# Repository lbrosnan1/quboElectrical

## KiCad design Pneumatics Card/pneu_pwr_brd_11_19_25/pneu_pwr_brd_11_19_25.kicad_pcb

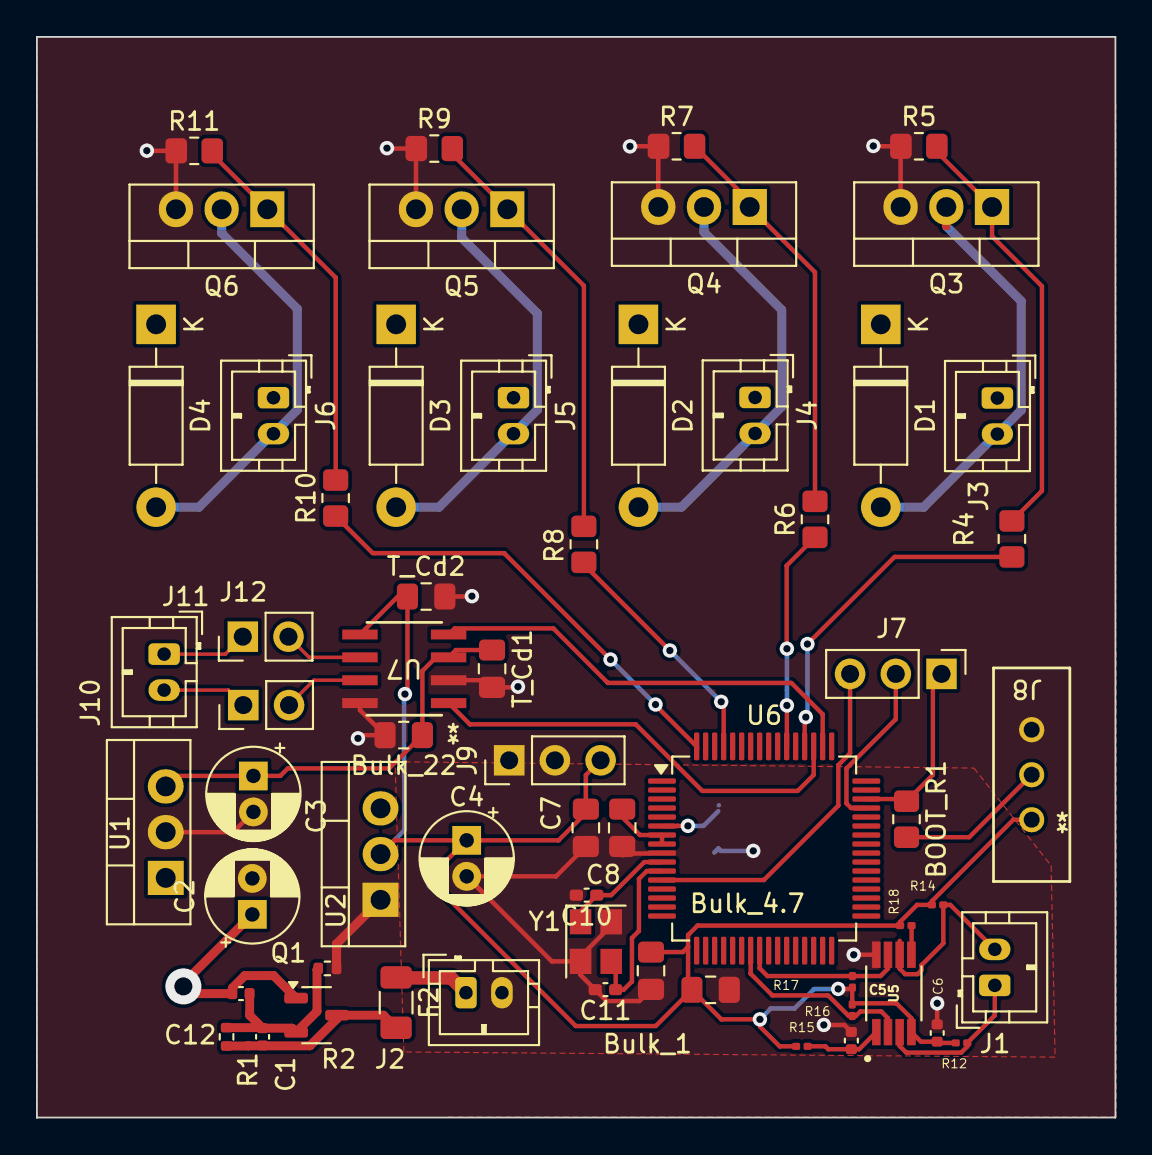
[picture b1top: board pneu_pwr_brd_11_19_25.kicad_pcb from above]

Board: 4 copper layers, 59.9 x 60.0 mm, 62 parts (1 on the bottom side), 36 nets.

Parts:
BOOT_R1: 10k; R_0805_2012Metric_Pad1.20x1.40mm_HandSolder
Bulk_1: 1uF; C_0805_2012Metric_Pad1.18x1.45mm_HandSolder
Bulk_4.7: 4.7uF; C_0805_2012Metric_Pad1.18x1.45mm_HandSolder
Bulk_22: 22uF; C_0805_2012Metric_Pad1.18x1.45mm_HandSolder
C1, C12: 4.7u; C_0402_1005Metric
C2, C3, C4: 10u; CP_Radial_D5.0mm_P2.00mm
C5, C6: 0.1u; C_0402_1005Metric
C7, C8, C9: 100nF; C_0805_2012Metric_Pad1.18x1.45mm_HandSolder
C10, C11: 10pF; C_0402_1005Metric_Pad0.74x0.62mm_HandSolder
D1, D2, D3, D4: 1N47xxA; D_DO-41_SOD81_P10.16mm_Horizontal
F2: 10A; Fuse_1206_3216Metric
J1, J2, J3, J4, J5, J6, J12: 2X1; JST_PH_B2B-PH-K_1x02_P2.00mm_Vertical
J7, J9: Conn_01x03_Pin; PinHeader_1x03_P2.54mm_Vertical
J8: Conn_01x03; slide_switch_EGER1218_Thruster
J10, J11: Conn_01x02; PinHeader_1x02_P2.54mm_Vertical
Q1: NTR0202PLT1G; SOT-23-3
Q3, Q4, Q5, Q6: FQP30N06L; TO-220-3_Vertical
R1: 47k; R_0402_1005Metric
R2: 100; R_0402_1005Metric
R4, R6, R8, R10: 330; R_0805_2012Metric_Pad1.20x1.40mm_HandSolder
R5, R7, R9, R11: 10k; R_0805_2012Metric_Pad1.20x1.40mm_HandSolder
R12, R14, R15, R16, R17, R18: 10k; C_0201_0603Metric
T_Cd1, T_Cd2: 100nF; C_0805_2012Metric_Pad1.18x1.45mm_HandSolder
U1: L7805; TO-220-3_Vertical
U2: LD1117V33; TO-220-3_Vertical
U5: TCA4307; SOP65P490X110-8N
U6: STM32G0B1RETx; LQFP-64_10x10mm_P0.5mm
U7: ATA6561-GAQW-N; SOIC8_4P9X3P9MC_MCH
Y1: 16Mhz; Crystal_SMD_3225-4Pin_3.2x2.5mm

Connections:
3.3V: Bulk_1.2, Bulk_4.7.1, C4.1, C6.2, C7.1, C8.1, J8.1, J9.3, R12.2, R14.1, R15.1, R16.2, R17.1, R18.1, T_Cd2.1, U2.2 (VO), U5.4 (VCC), U6.7 (VREF+), U6.8 (VDD), U7.5 (VIO)
5V: Bulk_22.1, C3.1, T_Cd1.1, U1.3 (OUT), U7.3 (VCC)
12V: C2.1, C12.2, D1.1 (K), D2.1 (K), D3.1 (K), D4.1 (K), J3.1, J4.1, J5.1, J6.1, Q1.1 (D), U1.1 (IN), U2.3 (VI)
+12V_fuse: F2.1, J2.1
/NRST: J7.3, U6.12 (PF2)
/SWCLK: BOOT_R1.1, J7.1, U6.46 (PA14)
/SWDIO: J7.2, U6.45 (PA13)
CAN+: J10.1, J10.2, J12.2, U7.7 (CANH)
CAN-: J11.1, J11.2, J12.1, U7.6 (CANL)
FDCAN_RX: U6.50 (PD0), U7.4 (RXD)
FDCAN_TX: U6.51 (PD1), U7.1 (TXD)
GND: Bulk_1.1, Bulk_4.7.2, Bulk_22.2, C2.2, C3.2, C4.2, C5.1, C6.1, C7.2, C8.2, C9.1, C10.2, C11.2, J2.2, J8.3, J9.1, J9.2, Q3.3 (S), Q4.3 (S), Q5.3 (S), Q6.3 (S), R2.1, R5.1, R7.1, R9.1, R11.1, T_Cd1.2, T_Cd2.2, U1.2 (GND), U2.1 (GND), U5.8 (GND), U6.9 (VSS), U7.2 (GND), U7.8 (STBY), Y1.2, Y1.4
unnamed: BOOT_R1.2, J8.2
unnamed: C1.1, C12.1, Q1.2 (G), R1.1, R2.2
unnamed: C1.2, F2.2, Q1.3 (S), R1.2
unnamed: Q3.1 (G), R4.2, R5.2
unnamed: Q4.1 (G), R6.2, R7.2
unnamed: Q5.1 (G), R8.2, R9.2
unnamed: Q6.1 (G), R10.2, R11.2
unnamed: C5.2, R15.2, U5.1 (EN)
unnamed: R18.2, U5.5 (READY)
RCC_OSC_IN: C10.1, U6.10 (PF0), Y1.1
RCC_OSC_OUT: C11.1, U6.11 (PF1), Y1.3
S1CTRL: R4.1, U6.52 (PD2)
S2CTRL: R6.1, U6.54 (PD4)
S3CTRL: R8.1, U6.61 (PB7)
S4CTRL: R10.1, U6.64 (PC10)
SCL: R17.2, U5.7 (SCLOUT), U6.24 (PA7)
SCL_ext: J1.2, R14.2, U5.6 (SCLIN)
SDA: R16.1, U5.2 (SDAOUT), U6.23 (PA6)
SDA_ext: J1.1, R12.1, U5.3 (SDAIN)
SLN1-: D1.2 (A), J3.2, Q3.2 (D)
SLN2-: D2.2 (A), J4.2, Q4.2 (D)
SLN3-: D3.2 (A), J5.2, Q5.2 (D)
SLN4-: D4.2 (A), J6.2, Q6.2 (D)
VBAT: C9.2, U6.6 (VBAT)

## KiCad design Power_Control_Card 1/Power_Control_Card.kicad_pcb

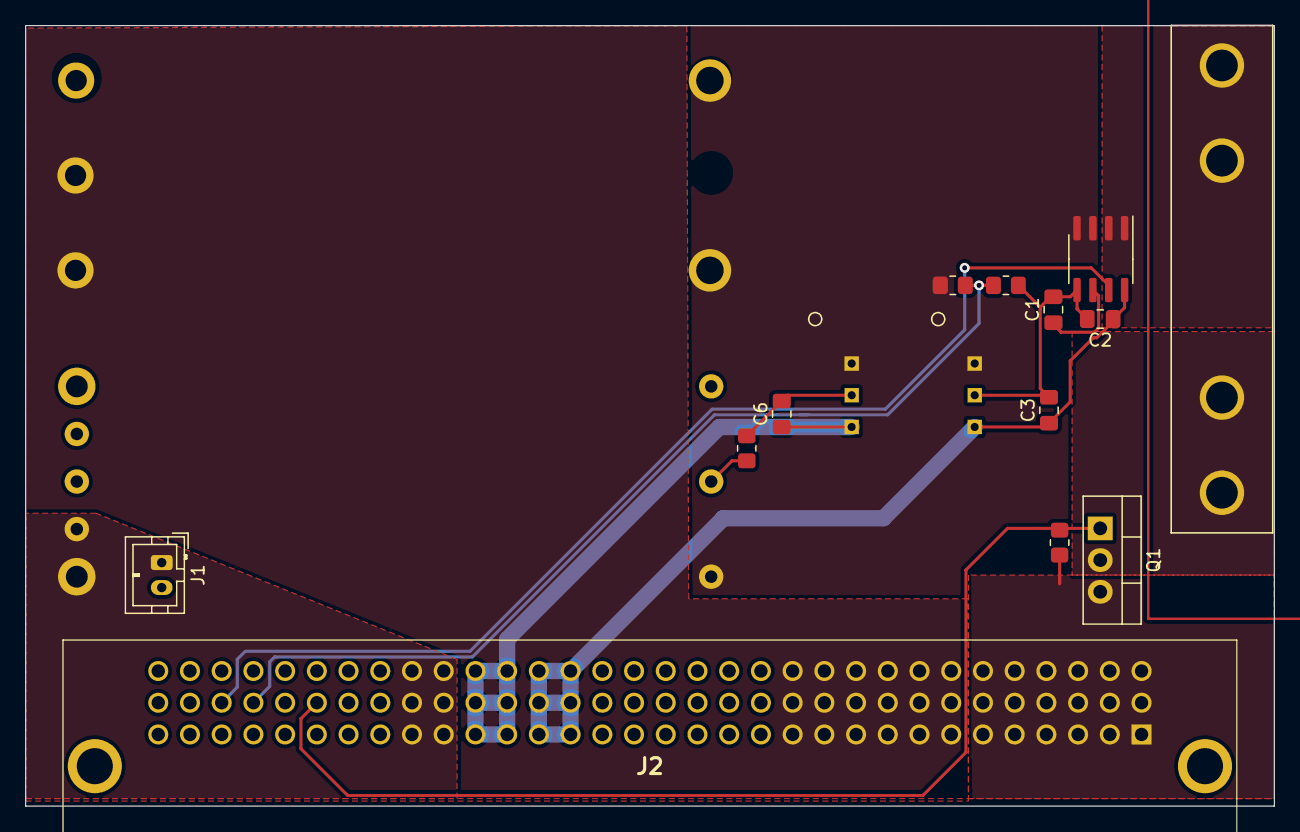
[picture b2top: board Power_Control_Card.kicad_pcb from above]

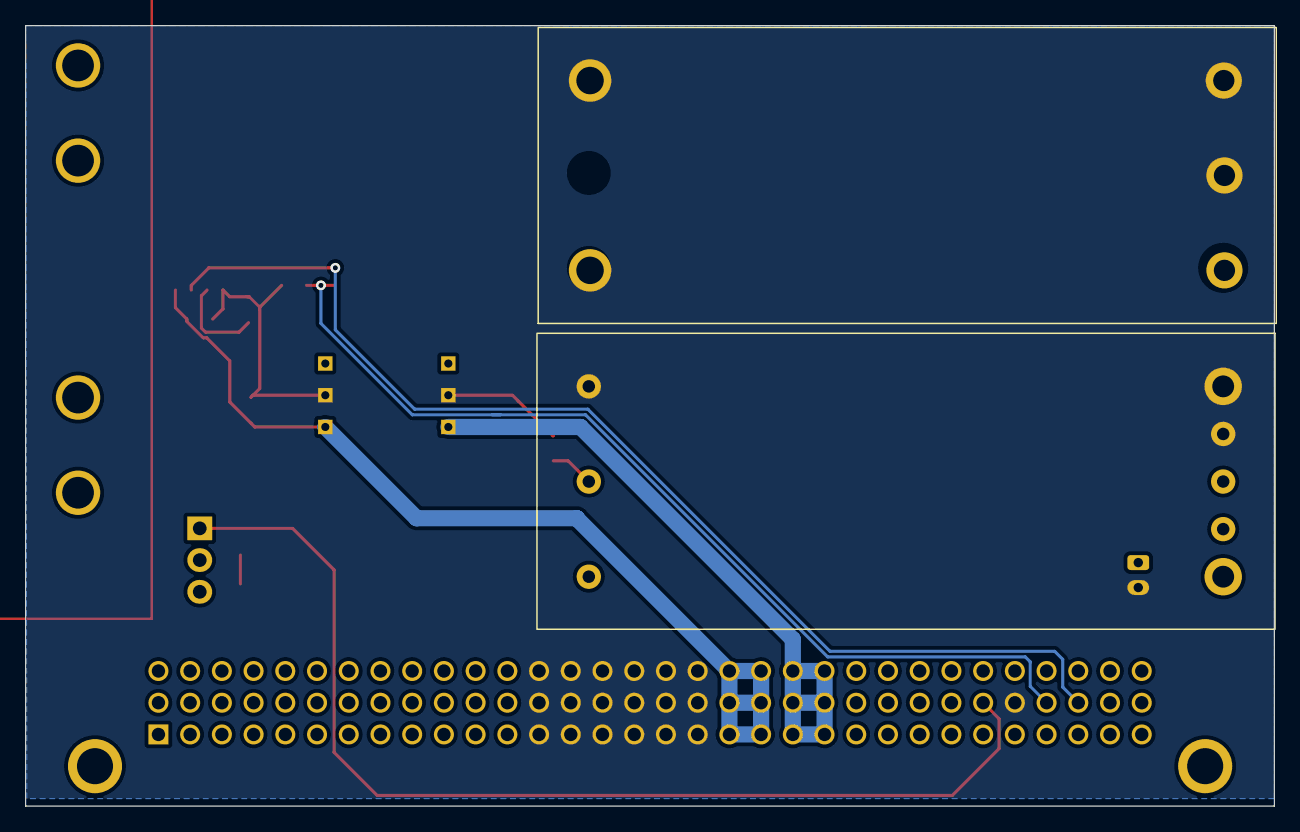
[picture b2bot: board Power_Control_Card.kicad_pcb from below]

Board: 2 copper layers, 100.0 x 62.5 mm, 17 parts (2 on the bottom side), 14 nets.

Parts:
20A1: Fuse; 1.25__FUSECLIPS
C1: 47n; C_0805_2012Metric_Pad1.18x1.45mm_HandSolder
C2: 0.1u; C_0805_2012Metric_Pad1.18x1.45mm_HandSolder
C3, C6: 1u; C_0805_2012Metric_Pad1.18x1.45mm_HandSolder
DC/DC_CNVRT1: TSR2-2450; TSR2
DC/DC_CNVRT2: TSR2-2433; TSR2
INPT_CRRNT_SNSR1: TMCS1101A4B; SOIC-8_3.9x4.9mm_P1.27mm
J1: Conn_01x02; JST_PH_B2B-PH-K_1x02_P2.00mm_Vertical
J2: 6509475
Q1: FQPF27P06; TO-220-3_Vertical
RSW1, RSW2: 10kO; R_0805_2012Metric_Pad1.20x1.40mm_HandSolder
U1: 240W_CONV
U2: 72W_CONV
VDIV1(R)1: 90kO; R_0805_2012Metric_Pad1.20x1.40mm_HandSolder
VDIV2(R)1: 10kO; R_0805_2012Metric_Pad1.20x1.40mm_HandSolder

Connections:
12V_Jetson: J1.1, J2.A23, J2.A24, J2.B23, J2.B24, J2.C23, J2.C24, U2.7 (SENSE+), U2.8 (VOUT)
+3.3V: C6.1, DC/DC_CNVRT2.3 (+V_OUT), J2.A21, J2.A22, J2.B21, J2.B22, J2.C21, J2.C22
+5V: C2.1, C3.1, DC/DC_CNVRT1.3 (+V_OUT), INPT_CRRNT_SNSR1.8 (VCC), J2.A19, J2.A20, J2.B19, J2.B20, J2.C19, J2.C20
+12V: J2.A7, J2.A8, J2.A9, J2.A10, J2.A11, J2.A12, J2.B7, J2.B8, J2.B9, J2.B10, J2.B11, J2.B12, J2.C7, J2.C8, J2.C9, J2.C10, J2.C11, J2.C12, U1.8 (VOUT)
+24V: J2.A1, J2.A2, J2.A3, J2.A4, J2.A5, J2.A6, J2.B1, J2.B2, J2.B3, J2.B4, J2.B5, J2.B6, J2.C1, J2.C2, J2.C3, J2.C4, J2.C5, J2.C6, Q1.3 (S), RSW1.1
/VBATT: 20A1.P$2 (4), INPT_CRRNT_SNSR1.1 (IP+)
/V_POWER: DC/DC_CNVRT1.1 (+V_IN), DC/DC_CNVRT2.1 (+V_IN), INPT_CRRNT_SNSR1.3 (IP-), U1.1 (VIN), U2.1 (VIN), VDIV1(R)1.1
DAT1: J2.B29, VDIV1(R)1.2, VDIV2(R)1.1
DAT2: INPT_CRRNT_SNSR1.7 (VIOUT), J2.B30
unnamed: 20A1.P$1 (1), Q1.2 (D)
unnamed: C1.1, INPT_CRRNT_SNSR1.6 (FILTER)
unnamed: RSW2.1, U2.2 (ON/OFF)
SW1: C1.2, C2.2, C3.2, C6.2, DC/DC_CNVRT1.2 (GND), DC/DC_CNVRT2.2 (GND), INPT_CRRNT_SNSR1.5 (GND), J1.2, J2.A13, J2.A14, J2.A15, J2.A16, J2.A17, J2.A18, J2.B13, J2.B14, J2.B15, J2.B16, J2.B17, J2.B18, J2.B28, J2.C13, J2.C14, J2.C15, J2.C16, J2.C17, J2.C18, RSW2.2, U1.3 (IN-), U1.4 (OUT-), U2.3 (IN-), U2.4 (OUT-), U2.5 (SENSE-), VDIV2(R)1.2
SW2: J2.B27, Q1.1 (G), RSW1.2

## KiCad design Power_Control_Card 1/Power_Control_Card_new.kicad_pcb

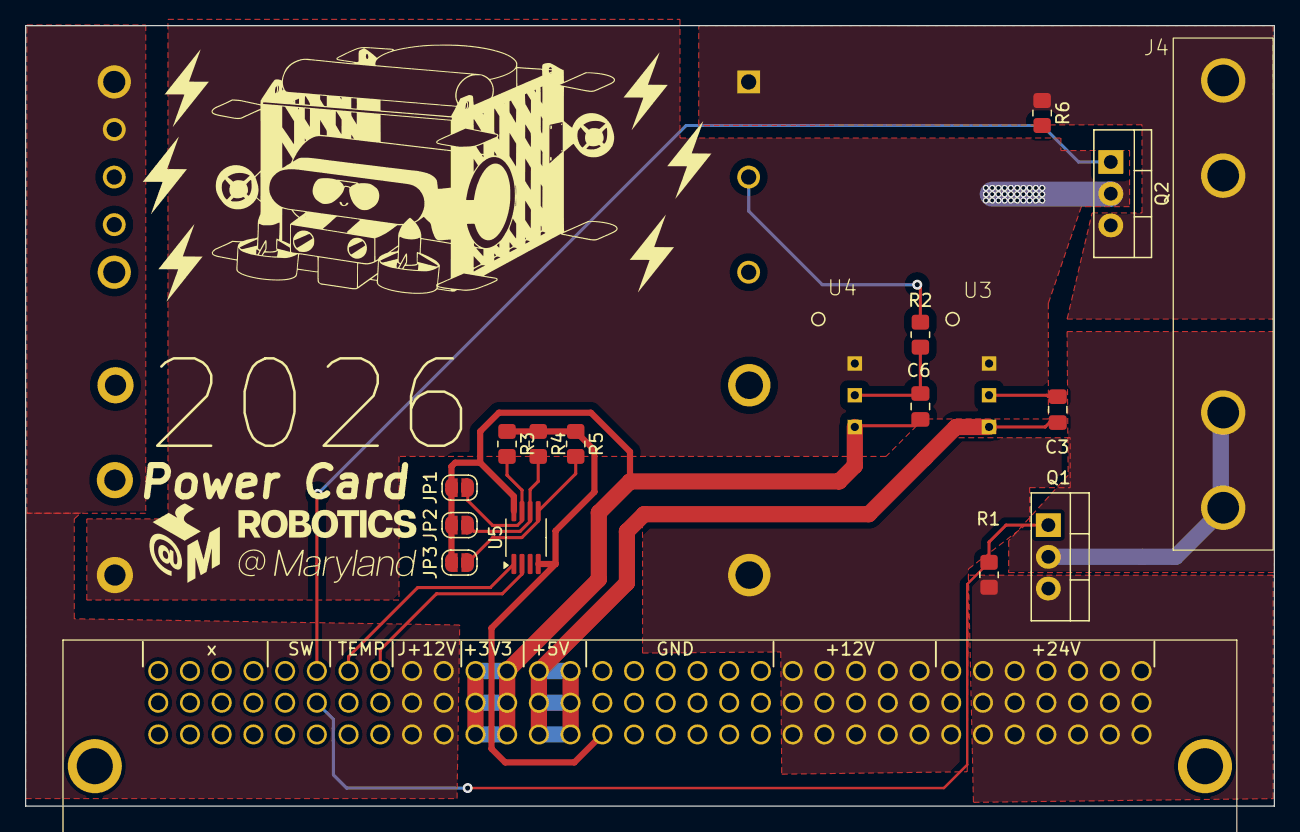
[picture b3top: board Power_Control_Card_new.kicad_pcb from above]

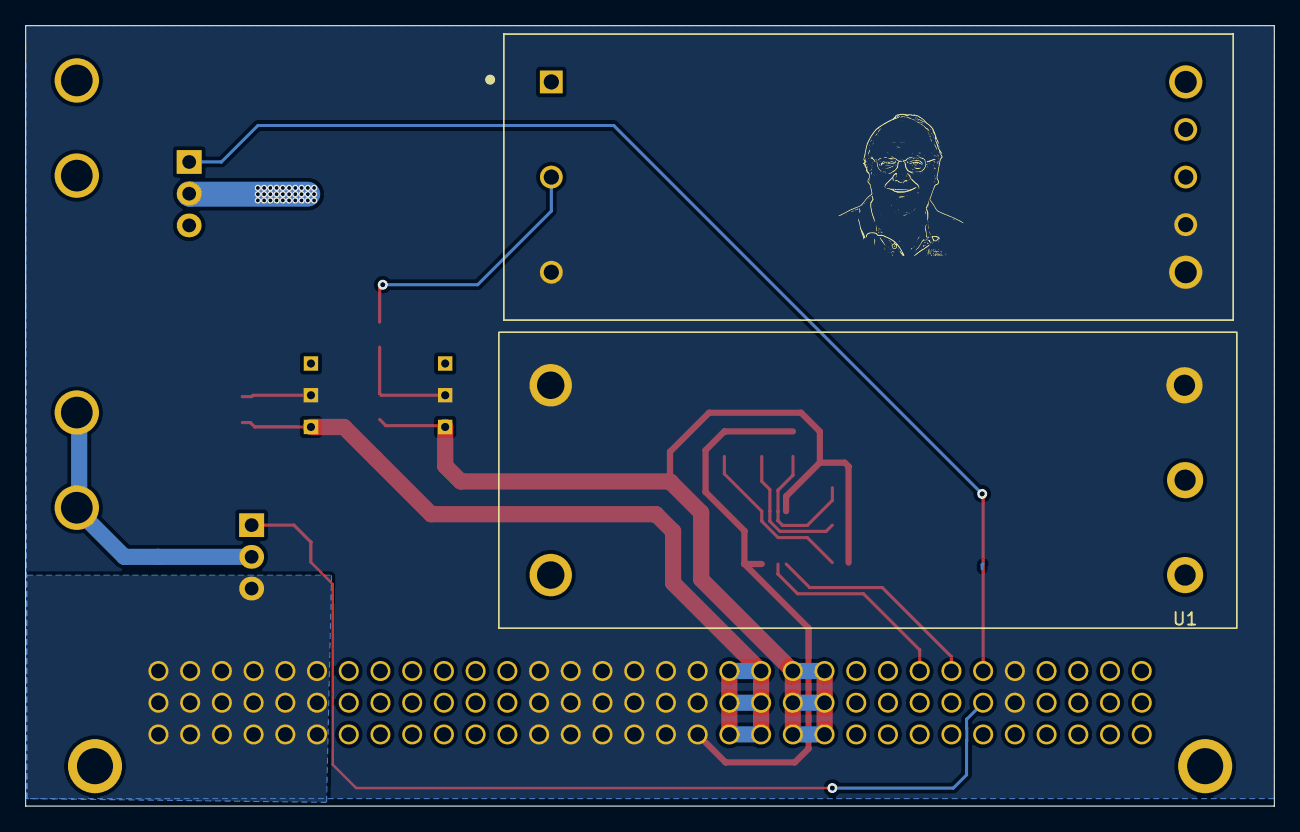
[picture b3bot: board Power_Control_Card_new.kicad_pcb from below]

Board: 2 copper layers, 100.0 x 62.5 mm, 20 parts (2 on the bottom side), 17 nets.

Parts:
C3, C6: 1u; C_0805_2012Metric_Pad1.18x1.45mm_HandSolder
J2: 6509475
J4: Conn_01x04_Pin; 1.25__FUSECLIPS
JP1, JP2, JP3: SolderJumper_2_Open; SolderJumper-2_P1.3mm_Open_RoundedPad1.0x1.5mm
Q1, Q2: FQPF27P06; TO-220-3_Vertical
R1, R2, R6: 10kO; R_0805_2012Metric_Pad1.20x1.40mm_HandSolder
R3, R4, R5: temp R; R_0805_2012Metric_Pad1.20x1.40mm_HandSolder
U1: 240W_CONV
U2: CONV_UWE-24_3-Q12P-C
U3: TSR2-2450; TSR2
U4: TSR2-2433; TSR2
U5: MCP9808_MSOP; MSOP-8_3x3mm_P0.65mm

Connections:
12V_Jetson: J2.A23, J2.A24, J2.B23, J2.B24, J2.C23, J2.C24, U2.7 (SENSE+), U2.8 (VOUT)
+3.3V: C6.1, J2.A21, J2.A22, J2.B21, J2.B22, J2.C21, J2.C22, JP1.1 (A), JP2.1 (A), JP3.1 (A), U4.3 (+V_OUT), U5.8 (V_{DD})
+5V: C3.1, J2.A19, J2.A20, J2.B19, J2.B20, J2.C19, J2.C20, U3.3 (+V_OUT)
+12V: J2.A7, J2.A8, J2.A9, J2.A10, J2.A11, J2.A12, J2.B7, J2.B8, J2.B9, J2.B10, J2.B11, J2.B12, J2.C7, J2.C8, J2.C9, J2.C10, J2.C11, J2.C12, U1.8 (VOUT)
+24V: J2.A1, J2.A2, J2.A3, J2.A4, J2.A5, J2.A6, J2.B1, J2.B2, J2.B3, J2.B4, J2.B5, J2.B6, J2.C1, J2.C2, J2.C3, J2.C4, J2.C5, J2.C6, Q1.3 (S), R1.1
/NonJetsonPower: Q2.2 (D), U1.1 (VIN), U3.1 (+V_IN), U4.1 (+V_IN)
/VBATT: J4.3, J4.4, Q2.3 (S), R6.1, U2.1 (VIN)
GND: C3.2, C6.2, J2.A13, J2.A14, J2.A15, J2.A16, J2.A17, J2.A18, J2.B13, J2.B14, J2.B15, J2.B16, J2.B17, J2.B18, J2.B28, J2.C13, J2.C14, J2.C15, J2.C16, J2.C17, J2.C18, J2.C28, R2.2, R3.1, R4.1, R5.1, U1.3 (IN-), U1.4 (OUT-), U2.3 (IN-), U2.4 (OUT-), U2.5 (SENSE-), U3.2 (GND), U4.2 (GND), U5.4 (GND)
NJSW1: J2.C27, Q2.1 (G), R6.2
unnamed: J4.1, J4.2, Q1.2 (D)
unnamed: JP1.2 (B), R3.2, U5.7 (A0)
unnamed: JP2.2 (B), R4.2, U5.6 (A1)
unnamed: JP3.2 (B), R5.2, U5.5 (A2)
unnamed: R2.1, U2.2 (ON/OFF)
SCL2: J2.C25, U5.2 (SCL)
SDA2: J2.C26, U5.1 (SDA)
SW2: J2.B27, Q1.1 (G), R1.2

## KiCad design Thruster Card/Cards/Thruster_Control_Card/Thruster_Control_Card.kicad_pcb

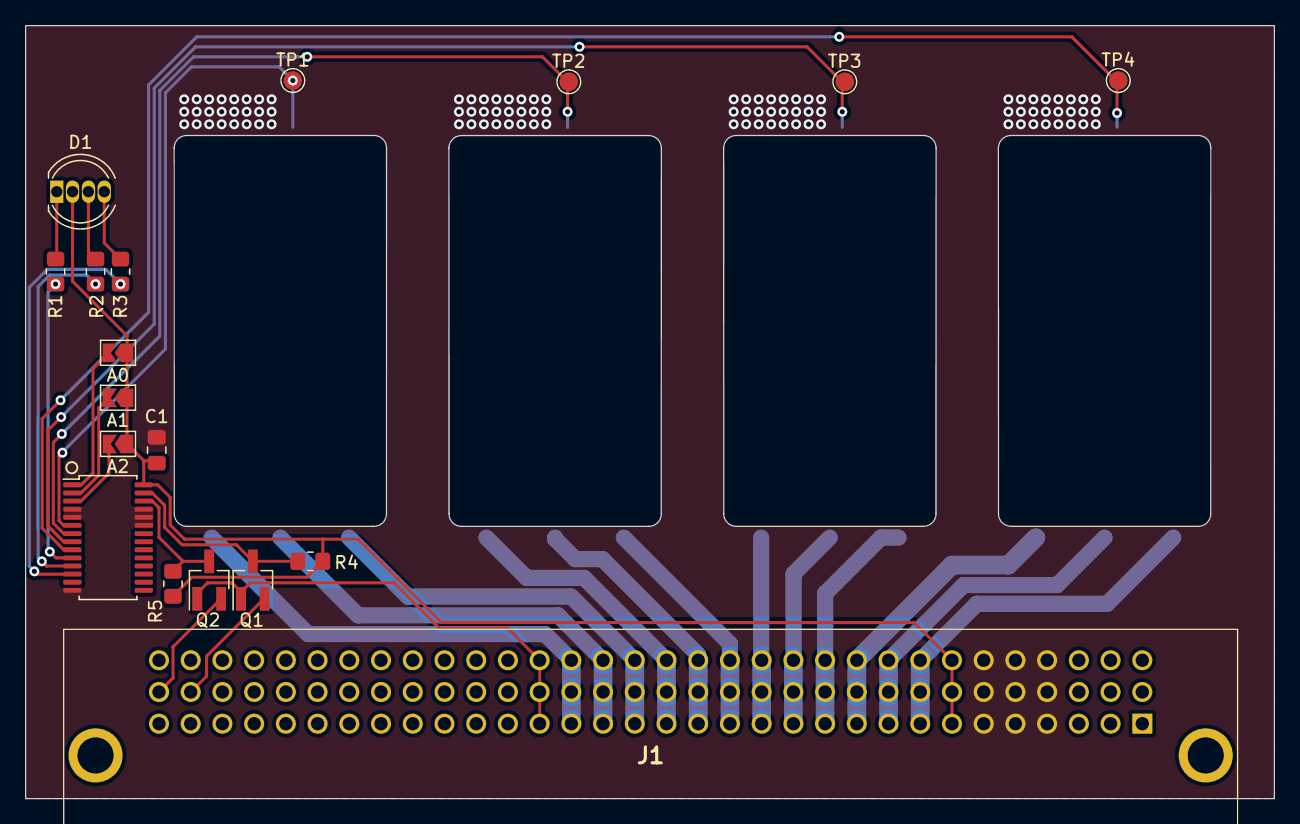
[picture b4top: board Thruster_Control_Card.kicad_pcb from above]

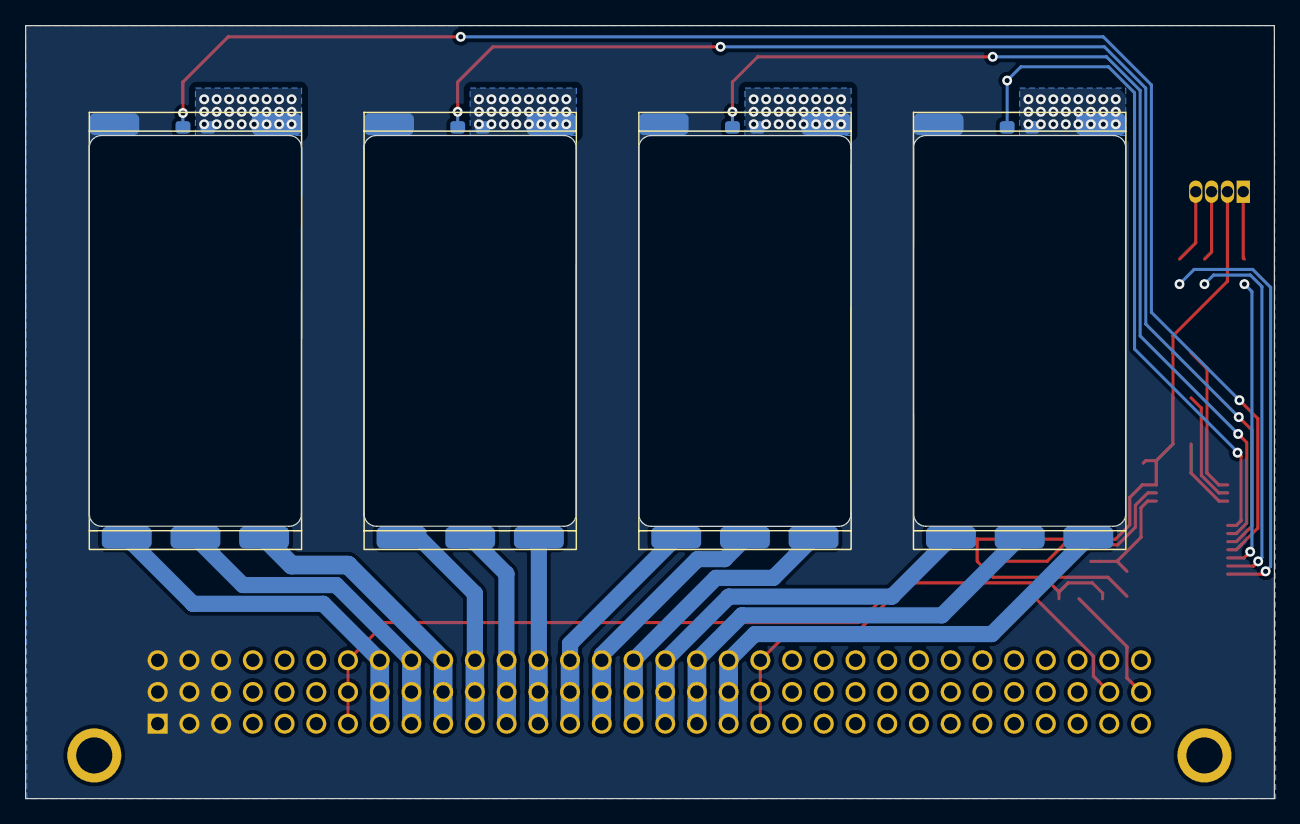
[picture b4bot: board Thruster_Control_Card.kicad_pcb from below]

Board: 4 copper layers, 100.0 x 61.9 mm, 22 parts (4 on the bottom side), 33 nets.

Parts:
A0, A1, A2: SolderJumper_2_Open; SolderJumper-2_P1.3mm_Open_TrianglePad1.0x1.5mm
C1: 10u; C_0805_2012Metric_Pad1.18x1.45mm_HandSolder
D1: LED_RGAB; LED_D5.0mm-4_RGB
I2C_PWM_DRIVER1: PCA9685; TSSOP-28_4.4x9.7mm_P0.65mm
J1: 6509475
Q1, Q2: BSS138; SOT-23_Handsoldering
R1, R2, R3: 220; R_0805_2012Metric_Pad1.20x1.40mm_HandSolder
R4, R5: 4.7kO; R_0805_2012Metric_Pad1.20x1.40mm_HandSolder
TP1, TP2, TP3, TP4: TestPoint; TestPoint_Pad_D1.5mm
U1, U2, U3, U4: ESC

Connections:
+3.3V: J1.A20, J1.B20, J1.C20, Q1.1 (G), Q2.1 (G)
+5V: A0.1 (A), A1.1 (A), A2.1 (A), C1.1, D1.2 (A), I2C_PWM_DRIVER1.28 (VDD), J1.A7, J1.B7, J1.C7, R4.2, R5.1
+12V: J1.A1, J1.A2, J1.A3, J1.B1, J1.B2, J1.B3, J1.C1, J1.C2, J1.C3, U1.1 (Vcc), U2.1 (Vcc), U3.1 (Vcc), U4.1 (Vcc)
/A1: J1.A17, J1.B17, J1.C17, U1.3 (A)
/A2: J1.A14, J1.B14, J1.C14, U2.3 (A)
/A3: J1.A11, J1.B11, J1.C11, U3.3 (A)
/A4: J1.A8, J1.B8, J1.C8, U4.3 (A)
/B1: J1.A18, J1.B18, J1.C18, U1.4 (B)
/B2: J1.A15, J1.B15, J1.C15, U2.4 (B)
/B3: J1.A12, J1.B12, J1.C12, U3.4 (B)
/B4: J1.A9, J1.B9, J1.C9, U4.4 (B)
/C1: J1.A19, J1.B19, J1.C19, U1.5 (C)
/C2: J1.A16, J1.B16, J1.C16, U2.5 (C)
/C3: J1.A13, J1.B13, J1.C13, U3.5 (C)
/C4: J1.A10, J1.B10, J1.C10, U4.5 (C)
/PWM1: I2C_PWM_DRIVER1.6 (PWM0), TP1.1, U1.6 (signal)
/PWM2: I2C_PWM_DRIVER1.7 (PWM1), TP2.1, U2.6 (signal)
/PWM3: I2C_PWM_DRIVER1.8 (PWM2), TP3.1, U3.6 (signal)
/PWM4: I2C_PWM_DRIVER1.9 (PWM3), TP4.1, U4.6 (signal)
/SCL: I2C_PWM_DRIVER1.26 (SCL), Q2.3 (S), R5.2
/SCL_IN: J1.B32, Q2.2 (D)
/SDA: I2C_PWM_DRIVER1.27 (SDA), Q1.3 (S), R4.1
/SDA_IN: J1.B31, Q1.2 (D)
GND: C1.2, I2C_PWM_DRIVER1.4 (A3), I2C_PWM_DRIVER1.5 (A4), I2C_PWM_DRIVER1.14 (GND), I2C_PWM_DRIVER1.23 (OE'), I2C_PWM_DRIVER1.24 (A5), I2C_PWM_DRIVER1.25 (EXTCLK), J1.A4, J1.A5, J1.A6, J1.B4, J1.B5, J1.B6, J1.C4, J1.C5, J1.C6, U1.2 (GND), U1.7 (pwm_gnd), U2.2 (GND), U2.7 (pwm_gnd), U3.2 (GND), U3.7 (pwm_gnd), U4.2 (GND), U4.7 (pwm_gnd)
unnamed: A0.2 (B), I2C_PWM_DRIVER1.1 (A0)
unnamed: A1.2 (B), I2C_PWM_DRIVER1.2 (A1)
unnamed: A2.2 (B), I2C_PWM_DRIVER1.3 (A2)
unnamed: D1.4 (BK), R3.1
unnamed: D1.3 (GK), R2.1
unnamed: D1.1 (RK), R1.1
unnamed: I2C_PWM_DRIVER1.10 (PWM4), R1.2
unnamed: I2C_PWM_DRIVER1.11 (PWM5), R2.2
unnamed: I2C_PWM_DRIVER1.12 (PWM6), R3.2
